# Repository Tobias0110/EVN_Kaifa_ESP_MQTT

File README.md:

# EVN Kaifa to MQTT
Allows you to read data from different kinds of smart power meters used by the
EVN power company in Austria. Data is read from the MBus interface (called Kundenschnittstelle P1),
packages are decrypted and then the values are sent to an MQTT endpoint. The
device hosts a webpage, where you can change your settings.

## 🤔 How does it work?
The ESP8266 receives the MBus data from the smart meter via a UART interface on the
front facing side of the device. A specially developed interface PCB powers the
micro-controller board from the MBus idle voltage (no extra power supply needed).
In addition, it contains a level shifter to convert from MBus voltage levels to
3V3 UART compatible with the ESP8266. This is useful because many people don't
have a power socket near their power meter.

The ESP8266 micro-controller syncs to the smartmeter's bursts of data so no packets
are lost. After receiving a package it is decrypted and the DSLM/COSEM data structure
is parsed to extract the measurement fields. These fields are then sent to an MQTT
broker in a preselected format. All relevant parameters can be configured via the
serial console at startup and are saved to the EEPROM.

Alternatively, you can update your configuration on the webpage that the ESP hosts
on the wifi network. The page is only accessible with a passcode that is set during
first setup. For more details on the webpage see below.

## 🔧 Installation
> **Note**
> Make sure the ESP is not connected to the interface board during programming or
> configuration.

The following steps are applicable if you are using the Arduino IDE to build the
project yourself.

1. Install [NodeJS](https://nodejs.org) on your machine, and navigate to the `www` directory.
   There, install the required npm packages by running `npm i` in your console.
2. Run the webpage build script. This should create a file named `settings-page.html.inl.h`
   next to the Arduino sketch file.
3. Install the ESP-Module as a compilation target.
    1. Add board config repository: File → Preferences →
       Paste URL into "Additional boards manager URLs": [http://arduino.esp8266.com/stable/package_esp8266com_index.json](http://arduino.esp8266.com/stable/package_esp8266com_index.json)
    2. Install the toolchain: Tools → Boards Manager → Install: esp8266
    3. Select the specific ESP module: Tools → Board → ESP2866 Boards → NodeMCU 1.0 (ESP-12E Modul)
4. Open the Library Manager pane and install the following dependecies.
    * [Crypto](https://github.com/rweather/arduino-projects) by Rhys Weatherley
    * [PubSubClient](https://github.com/knolleary/pubsubclient) by Nicholas O'Leary
    * [CRC](https://github.com/RobTillaart/CRC) by Rob Tillaart
5. Manully install the following dependencies by downloading their source code and
   dropping it into your `Arduino/Libraries` directory.
    * [ESPTrueRandom8266](https://github.com/marvinroger/ESP8266TrueRandom) by Marvin Roger
6. Click verify to check if the project builds without errors.
7. Connect the ESP module and click upload like for any other Arduino-like micro controller.
8. Connect to the ESP2866 through the serial monitor and start configuration.

## ⚙ Configuration via serial
> **Note**
> Make sure the ESP is not connected to the interface board during programming or
> configuration.

First configuration of the device is done via the serial terminal and is guided
by an interactive setup wizard. On first startup the checksum check will fail and
you will be required to enter settings. Later, you can enter the setup wizard
again during the first 10 seconds after starting by pressing 's'. You can also
clear your configuration by pressing 'c'.

1. Connect the ESP board via USB to your computer and open a serial terminal.
   Serial settings: 115200 Baud, NO Parity
2. Press reset on the ESP board.
3. On first startup the setup wizard starts immediately. Else press 's' on your
   keyboard when you are prompted to do so to edit the current settings.
4. The configuration wizard shows each settings field. Enter the data for each field
   and press return. Some fields come with default values, which are accepted by
   pressing return without any other input.
5. After start up the system switches the serial interface to MBus mode (2400 baud,
  even parity) and waits for data packets.

To boot the ESP with your settings, reset the micro-controller. All the settings fields that
can be configured are listed in the table below.

| Field name | Default value | Description |
| :--- | :--- | :--- |
WiFi SSID || SSID of the WiFi station to connect to |
WiFI password || Password of the WiFi station to connect to |
MQTT broker network address || Domain/IP of the MQTT broker server |
MQTT broker network port | 1883 | Network port of the MQTT broker server |
MQTT broker certificate fingerprint | [insecure] | SHA1 fingerprint of the SSL certificate of the MQTT broker server as hex string. If set to `[insecure]` TLS is disabled and all data is sent as plaint text |
MQTT broker user name | power-meter | User name to authenticate at the MQTT broker server |
MQTT broker password || Password to authenticate at the MQTT broker server |
MQTT broker client id || Client id to register as at the MQTT broker server |
MQTT broker path || Base path prepended to MQTT topics |
MQTT message mode | 2 | Selects the format for sending the data fields to the MQTT broker server (0 - raw, 1 - topics, 2 - json) |
Webpage key | _automatically generated random value_ | Passkey to access the webpage |
DSLM/COSEM decryption key (meter key) || Decryption key to decipher the MBus data packets provided by the power company |

> **Note**
> When reconnecting the micro-controller PCB to the interface PCB make sure that the pins align correctly.
> Also check that the USB connector points in the direction of the M-Bus connector. Wrong positioning can result in a short and damage the microcontroler.

## 🌍 Configuration via webpage
After initial setup with the serial interface and having the ESP connected to
the wifi, you can connect to the configuration webpage. To access it you need
the passkey you set before.

Due to memory limitation of the ESP8266 only a single TLS tunnel can be used at
once. As one is needed for the secure mqtt connection, there are no resources left
for the webserver. Therefore an alternative security scheme is used and the
page is hosted as plain HTTP. This means, that all your settings are always
transmitted encrypted and unreadable to others.

For security reasons, especially sensitive fields are not automatically populated
in their respective form fields. When you edited any settings and saved your changes
they will only take effect after restarting the device.

## 📬 MQTT output formats
> **Note**
> 🔐 When using secure MQTT, make sure to put `tls_version tlsv1.2` in your MQTT
> servers config file, so it only accepts encrypted connections!

The system can be configured to output the data received from the smartmeter in one
of the following formats.

### 🥩 Raw
The decryptd raw data without DSLM/COSEM parsing is sent to the broker at
`<basepath/raw>`. The data is sent as binary.

### 🐧 JSON
If the data is serialized as JSON, it is sent to the broker at `<basepath>/json`.
The json object has the following format.

| Field name  | Type          | Full name  | Description |
| :---------- | :------------ | :--------- | :--- |
| meternumber | string[12]    || The unique identification number of the smartmeter |
| timestamp   | ISO timestamp || Time when the measurement was taken |
| w_p         | number        | positive total energy | Total energy consumed |
| w_n         | number        | negative total energy | Total energy sent back to the grid |
| p_p         | number        | positive momentary power | Power currently consumed |
| p_n         | number        | negative momentary power | Power currently sent back to the grid |
| u1          | number        | voltage on phase 1 | Momentary voltage measured on phase 1 |
| u2          | number        | voltage on phase 2 | Momentary voltage measured on phase 2 |
| u3          | number        | voltage on phase 3 | Momentary voltage measured on phase 3 |
| i1          | number        | current on phase 1 | Momentary current measured on phase 1 |
| i2          | number        | current on phase 2 | Momentary current measured on phase 2 |
| i3          | number        | current on phase 3 | Momentary current measured on phase 3 |
| phi         | number        | power factor | Momentary power factor |
| ip          | string        || IP address received via DHCP |
| rssi        | string        | Received Signal Strength Indicator | Strength of the wifi signal in `dBm` |

The following JSON is an example package sent by the micro-controller.
```json
{
  "meternumber": "181220000009",
  "timestamp": "2021-09-27T09:47:15+02:00",
  "w_p": 12937,
  "w_n": 0,
  "p_p": 0,
  "p_n": 0,
  "u1": 233.7,
  "u2": 0,
  "u3": 0,
  "i1": 0,
  "i2": 0,
  "i3":0 ,
  "phi":1.000,
  "ip": "192.168.143.51",
  "rssi": "-52dBm"
}
```

### 🔬 Individual topics
If the data fields are sent to individual mqtt topics the following paths are used.
For a description of the fields checkout the section above.

| Field name               | Full name  |
| :----------------------- | :--------- |
| `<basepath>/meternumber` ||
| `<basepath>/timestamp`   ||
| `<basepath>/w_p`         | positive total energy |
| `<basepath>/w_n`         | negative total energy |
| `<basepath>/p_p`         | positive momentary power |
| `<basepath>/p_n`         | negative momentary power |
| `<basepath>/u1`          | voltage on phase 1 |
| `<basepath>/u2`          | voltage on phase 2 |
| `<basepath>/u3`          | voltage on phase 3 |
| `<basepath>/i1`          | current on phase 1 |
| `<basepath>/i2`          | current on phase 2 |
| `<basepath>/i3`          | current on phase 3 |
| `<basepath>/phi`         | power factor |

## ☔ Standard compliance
The parsing of MBus packets, and the deserialization of the DSLM/COSEM data is
based on reverse engineering work done by [@Tobias0110](https://www.github.com/Tobias0110)
and [@PreyMa](https://www.github.com/PreyMa) as the documents defining the standard are not
publicly accessible. So there is no guarantee that anything behaves as expected,
but we try to thoroughly test the software on real hardware.

Thanks to Austrian laws power companies are required to describe how the P1 interface
on their smartmeters works at least to some degree. The following resources were
useful to understand how the communication should be implemented:

* [M-Bus Specification](https://m-bus.com/assets/downloads/MBDOC48.PDF) (version "late 90s"):
* Smart meter customer data port description (Multiple Austrian energy companies):
  * [EVN](https://www.netz-noe.at/Download-(1)/Smart-Meter/218_9_SmartMeter_Kundenschnittstelle_lektoriert_14.aspx)
  * [Stadtwerke Schwaz](https://stadtwerkeschwaz.at/pdfs/Technische%20Beschreibung%20Kundenschnittstelle%20SWS%20Smart%20Meter.pdf)
  * [Salzburg Netz](https://www.salzburgnetz.at/content/dam/salzburgnetz/dokumente/stromnetz/Technische-Beschreibung-Kundenschnittstelle.pdf)
  * [Tinetz](https://www.tinetz.at/infobereich/smart-meter/anleitungen-fragen-antworten/?no_cache=1&tx_bh_page%5Baction%5D=download&tx_bh_page%5Bcontroller%5D=File&tx_bh_page%5Bfile%5D=101&cHash=7b38017b8f4066394c0f5119ee1ae342)
* Python implementation of a [DLMS to XML converter](https://github.com/Gurux/Gurux.DLMS.Python/)

## ⚒ Hardware

New in Version 2:
* M-Bus over voltage protection: Protects the DC/DC converter from voltages outside its specs.
* EMC improvements of the DC/DC converter.
* Space for alternative Zener diodes to allow diffrent logic levels on the M-Bus.
* Big capacitor can be alternatively placed on the bottom side of the PCB.
* Markings for how to connect the microcontroller correctly.
* Warning to disconnect the microcontroller for programming is now on the bottom side.

## 📋 Feature roadmap
* [X] Output the clock of the smart meter in UTC
* [X] Output the smartmeter's unique id (Zählernummer)
* [X] Implement the M-Bus library and parse DSLM/COSEM data
* [X] MQTT SSL
* [X] Web server for configuration
* [ ] Expand the software to support all M-Bus smart meters in Austria
* [ ] Support for the Improv Serial standard for WiFi configuration

## 🤝 Support the project
You can support the project by purchasing the custom hardware designed by @Tobias0110.
Contact Tobias via oe3tec(at)egimoto.com

If you want to contribute to the project feel free to hack on the code and open a
pull-request. Let us know if you find any bugs or issues.

## 📜 License
This project is licensed under the GPL v2.0.

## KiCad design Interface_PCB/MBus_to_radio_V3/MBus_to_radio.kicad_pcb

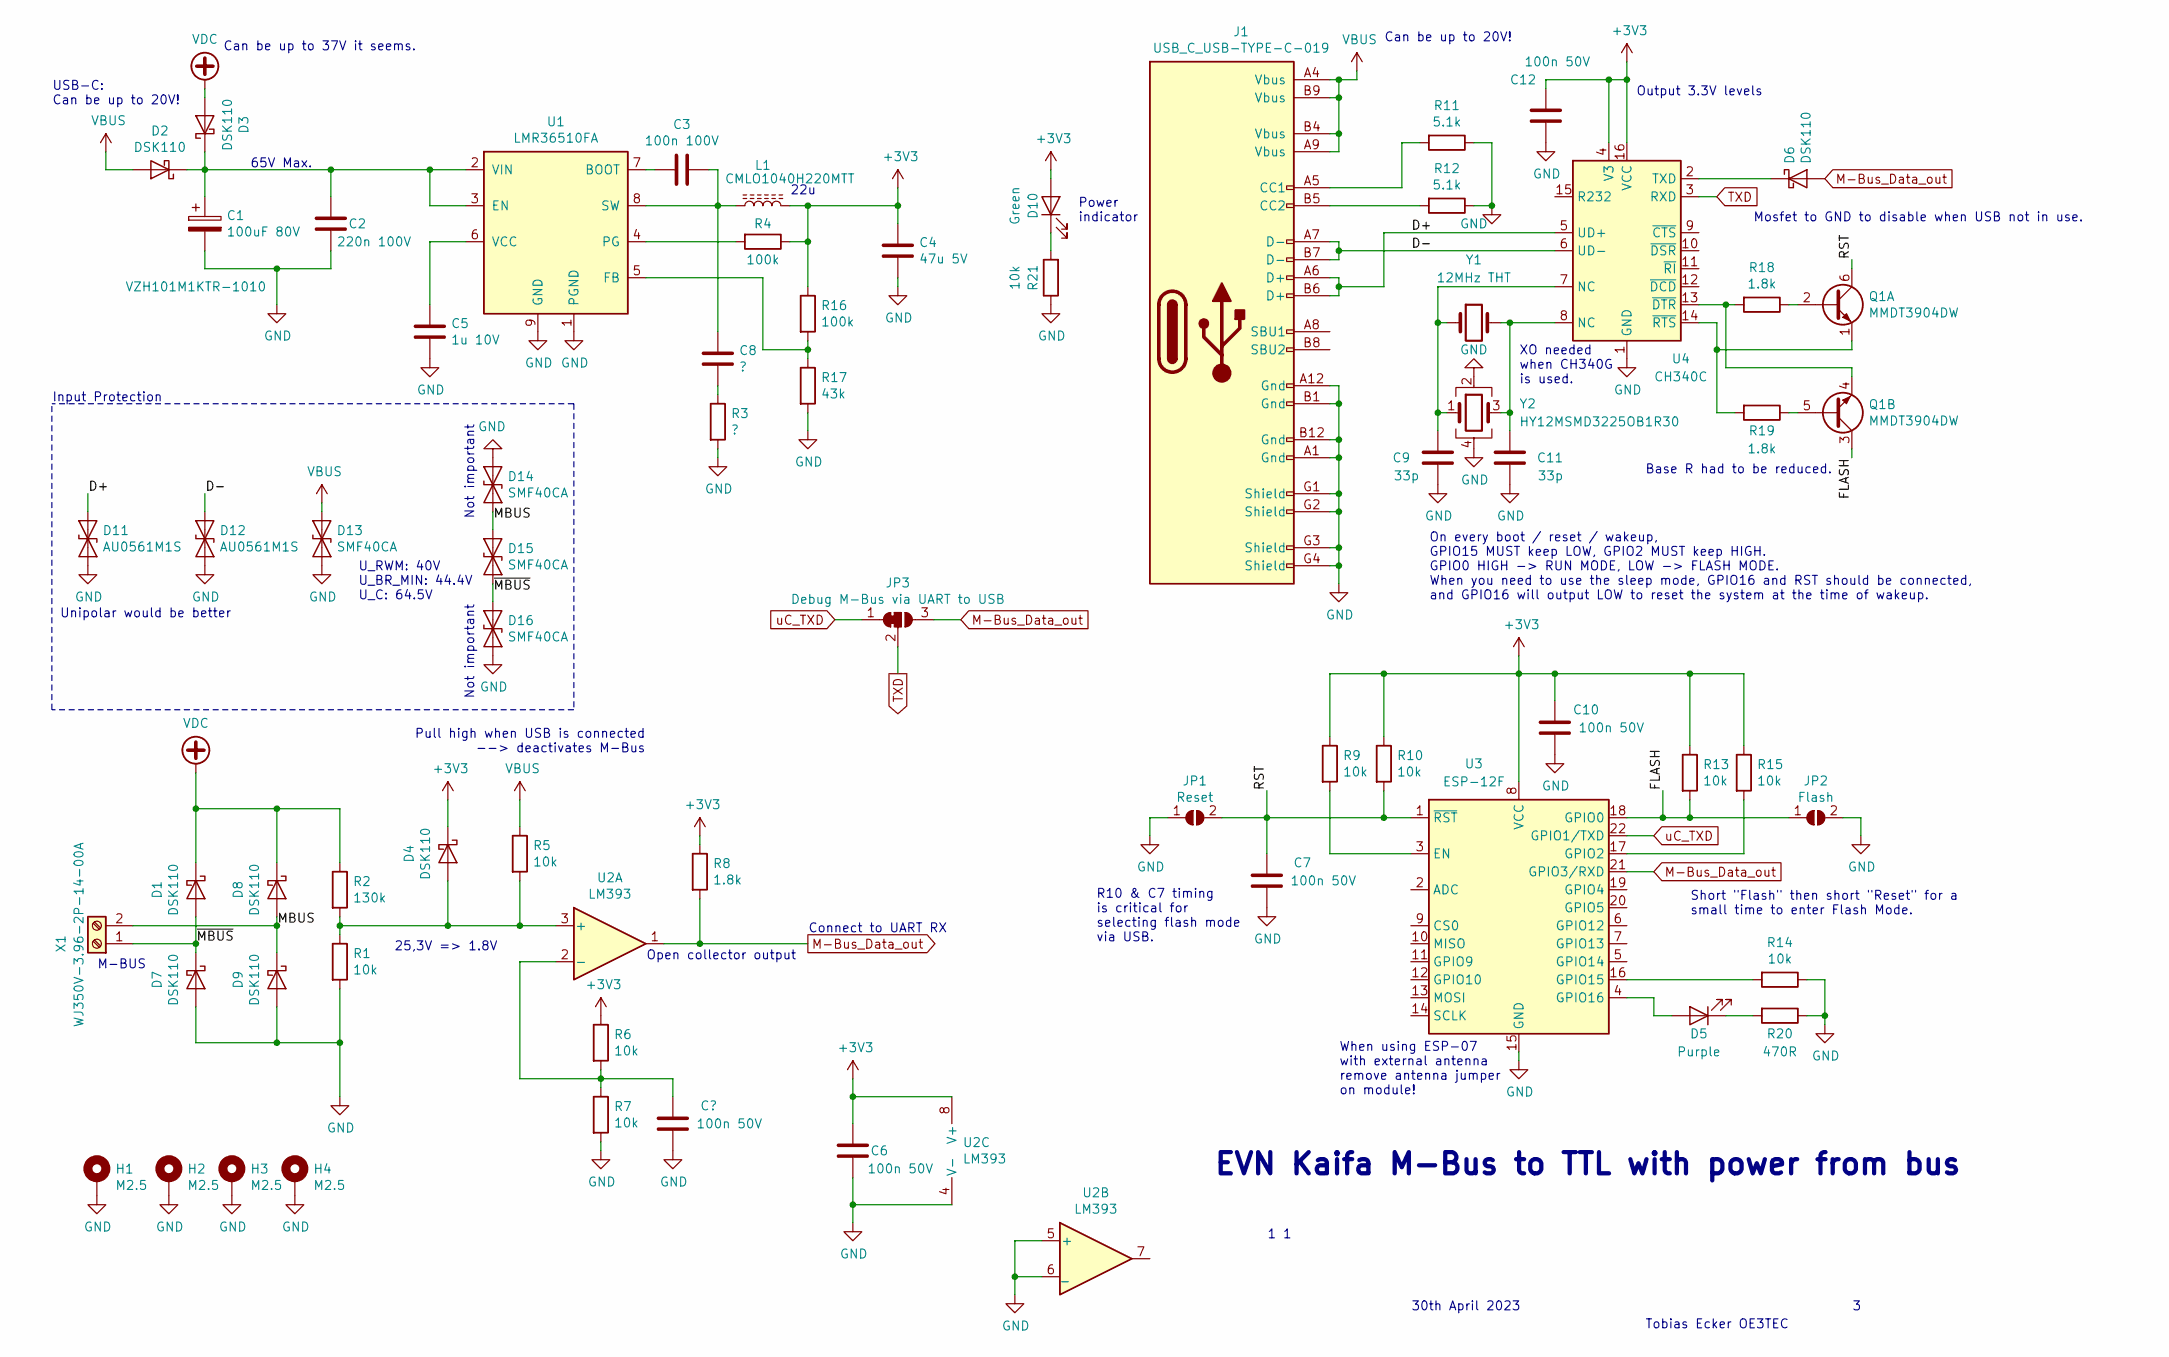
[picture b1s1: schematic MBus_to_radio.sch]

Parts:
C1: 100uF 80V; CP_Elec_10x10
C2: 220n 100V; C_1206_3216Metric
C3: 100n 100V; C_0603_1608Metric
C4: 47u 5V; C_1206_3216Metric
C5: 1u 10V; C_0603_1608Metric
C6, C7, C10, C12: 100n 50V; C_0603_1608Metric
C8: ?; C_0603_1608Metric
C9, C11: 33p; C_0402_1005Metric
D1, D2, D3, D4, D6, D7, D8, D9: DSK110; D_SOD-123
D5: Purple; LED_0402_1005Metric
D10: Green; LED_0402_1005Metric
D11, D12: AU0561M1S; D_0402_1005Metric
D13, D14, D15, D16: SMF40CA; D_SOD-123F
H1, H2, H3, H4: M2.5; MountingHole_2.5mm_Pad_Via
J1: USB_C_USB-TYPE-C-019; USB-TYPE-C-019
JP1: Reset; SolderJumper-2_P1.3mm_Open_RoundedPad1.0x1.5mm
JP2: Flash; SolderJumper-2_P1.3mm_Open_RoundedPad1.0x1.5mm
JP3: Debug M-Bus via UART to USB; SolderJumper-3_P1.3mm_Bridged12_RoundedPad1.0x1.5mm_NumberL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
L1: CMLO1040H220MTT; L_10.4x10.4_H4.8
Q1: MMDT3904DW; SOT-363_SC-70-6
R1: 10k; R_0603_1608Metric
R2: 130k; R_0603_1608Metric
R3: ?; R_0603_1608Metric
R4: 100k; R_0603_1608Metric
R5, R6, R7, R9, R10, R13, R14, R15, R21: 10k; R_0402_1005Metric
R8, R18, R19: 1.8k; R_0402_1005Metric
R11, R12: 5.1k; R_0402_1005Metric
R16: 100k; R_0402_1005Metric
R17: 43k; R_0402_1005Metric
R20: 470R; R_0402_1005Metric
U1: LMR36510FA; SOIC-8-1EP_3.9x4.9mm_P1.27mm_EP2.29x3mm_ThermalVias
U2: LM393; SOIC-8_3.9x4.9mm_P1.27mm
U3: ESP-12F; ESP-12E
U4: CH340C; SOIC-16_3.9x9.9mm_P1.27mm
X1: WJ350V-3.96-2P-14-00A
Y1: 12MHz THT; Crystal_HC49-U_Vertical
Y2: HY12MSMD3225OB1R30; Crystal_SMD_EuroQuartz_MT-4Pin_3.2x2.5mm

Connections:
+3V3: C4.2, C6.2, C10.2, C12.2, D4.1 (K), D10.2 (A), L1.2, R4.1, R6.1, R8.1, R9.1, R10.1, R13.1, R15.1, R16.1, U2.8 (V+), U3.8 (VCC), U4.4 (V3), U4.16 (VCC)
/D+: D11.1 (A1), J1.A6 (D+), J1.B6 (D+), U4.5 (UD+)
/D-: D12.1 (A1), J1.A7 (D-), J1.B7 (D-), U4.6 (UD-)
/FLASH: JP2.1 (A), Q1.3 (C2), R13.2, U3.18 (GPIO0)
/MBUS: D8.2 (A), D9.1 (K), D14.2 (A2), D15.1 (A1), X1.2
/RST: C7.2, JP1.2 (B), Q1.6 (C1), R10.2, U3.1 (~RST)
/~MBUS: D1.2 (A), D7.1 (K), D15.2 (A2), D16.1 (A1), X1.1
GND: C1.2, C2.1, C4.1, C5.1, C6.1, C7.1, C9.1, C10.1, C11.1, C12.1, D7.2 (A), D9.2 (A), D11.2 (A2), D12.2 (A2), D13.2 (A2), D14.1 (A1), D16.2 (A2), H1.1, H2.1, H3.1, H4.1, J1.A1 (Gnd), J1.A12 (Gnd), J1.B1 (Gnd), J1.B12 (Gnd), J1.G1 (Shield), J1.G2 (Shield), J1.G3 (Shield), J1.G4 (Shield), JP1.1 (A), JP2.2 (B), R1.2, R3.2, R7.2, R11.1, R12.1, R14.1, R17.2, R20.1, R21.1, U1.1 (PGND), U1.9 (GND), U2.4 (V-), U2.5 (+), U2.6 (_), U3.15 (GND), U4.1 (GND), Y2.2, Y2.4
M-Bus_Data_out: D6.2 (A), JP3.3 (B), R8.2, U2.1, U3.21 (GPIO3/RXD)
unnamed: C1.1, C2.2, D2.1 (K), D3.1 (K), U1.2 (VIN), U1.3 (EN)
unnamed: C3.1, U1.7 (BOOT)
unnamed: C3.2, C8.2, L1.1, U1.8 (SW)
unnamed: C5.2, U1.6 (VCC)
unnamed: C8.1, R3.1
unnamed: C9.2, U4.7 (NC), Y1.1, Y2.1
unnamed: C11.2, U4.8 (NC), Y1.2, Y2.3
unnamed: D4.2 (A), R1.1, R2.2, R5.2, U2.3 (+)
unnamed: D5.1 (K), R20.2
unnamed: D5.2 (A), U3.4 (GPIO16)
unnamed: D6.1 (K), U4.2 (TXD)
unnamed: D10.1 (K), R21.2
unnamed: J1.A5 (CC1), R11.2
unnamed: J1.B5 (CC2), R12.2
unnamed: Q1.1 (E1), R19.2, U4.14 (~RTS)
unnamed: Q1.2 (B1), R18.1
unnamed: Q1.4 (E2), R18.2, U4.13 (~DTR)
unnamed: Q1.5 (B2), R19.1
unnamed: R4.2, U1.4 (PG)
unnamed: R6.2, R7.1, U2.2 (-)
unnamed: R9.2, U3.3 (EN)
unnamed: R14.2, U3.16 (GPIO15)
unnamed: R15.2, U3.17 (GPIO2)
unnamed: R16.2, R17.1, U1.5 (FB)
TXD: JP3.2 (C), U4.3 (RXD)
VBUS: D2.2 (A), D13.1 (A1), J1.A4 (Vbus), J1.A9 (Vbus), J1.B4 (Vbus), J1.B9 (Vbus), R5.1
VDC: D1.1 (K), D3.2 (A), D8.1 (K), R2.1
uC_TXD: JP3.1 (A), U3.22 (GPIO1/TXD)

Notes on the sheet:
EVN Kaifa M-Bus to TTL with power from bus
1 1
30th April 2023
Tobias Ecker OE3TEC
Connect to UART RX
Pull high when USB is connected --> deactivates M-Bus
Open collector output
Short "Flash" then short "Reset" for a small time to enter Flash Mode.
25,3V => 1.8V
On every boot / reset / wakeup, GPIO15 MUST keep LOW, GPIO2 MUST keep HIGH. GPIO0 HIGH -> RUN MODE, LOW -> FLASH MODE. When you need to use the sleep mode, GPIO16 and RST should be connected, and GPIO16 will output LOW to reset the system at the time of wakeup.
65V Max.
XO needed when CH340G is used.
Output 3.3V levels
R10 & C7 timing is critical for selecting flash mode via USB.
When using ESP-07 with external antenna remove antenna jumper on module!
M-BUS
Power indicator
22u
Can be up to 20V!
USB-C: Can be up to 20V!
Can be up to 37V it seems.
Input Protection
U_RWM: 40V U_BR_MIN: 44.4V U_C: 64.5V
Not important
Unipolar would be better
Base R had to be reduced.
Mosfet to GND to disable when USB not in use.

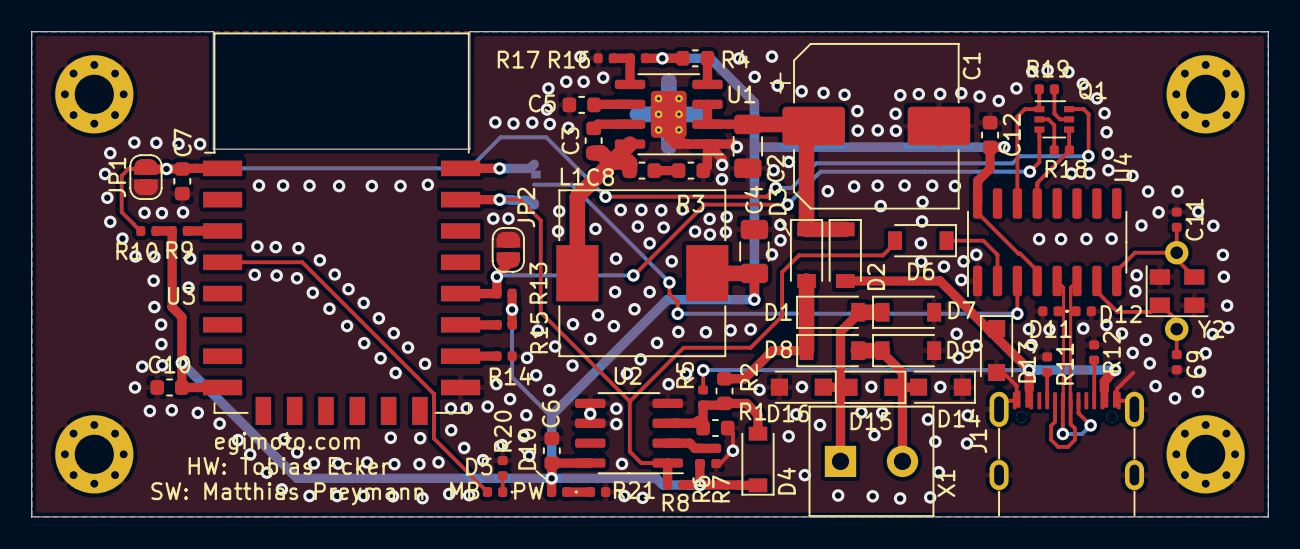
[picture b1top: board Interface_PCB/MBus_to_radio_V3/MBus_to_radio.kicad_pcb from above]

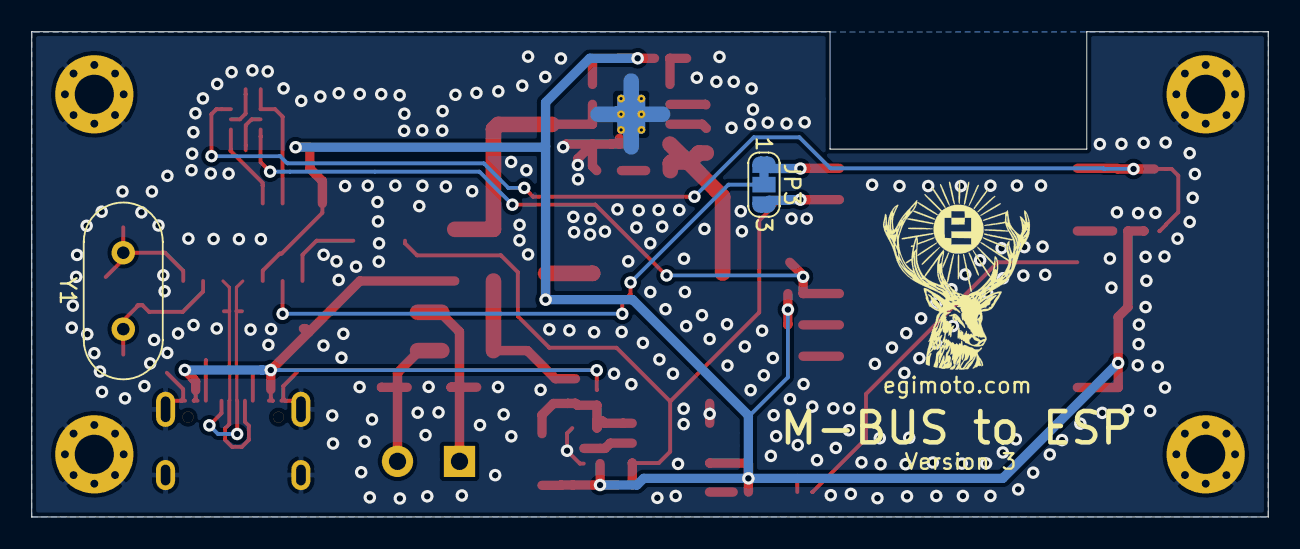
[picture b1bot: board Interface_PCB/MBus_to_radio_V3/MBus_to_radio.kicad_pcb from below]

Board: 2 copper layers, 79.0 x 31.0 mm, 66 parts (2 on the bottom side), 37 nets.

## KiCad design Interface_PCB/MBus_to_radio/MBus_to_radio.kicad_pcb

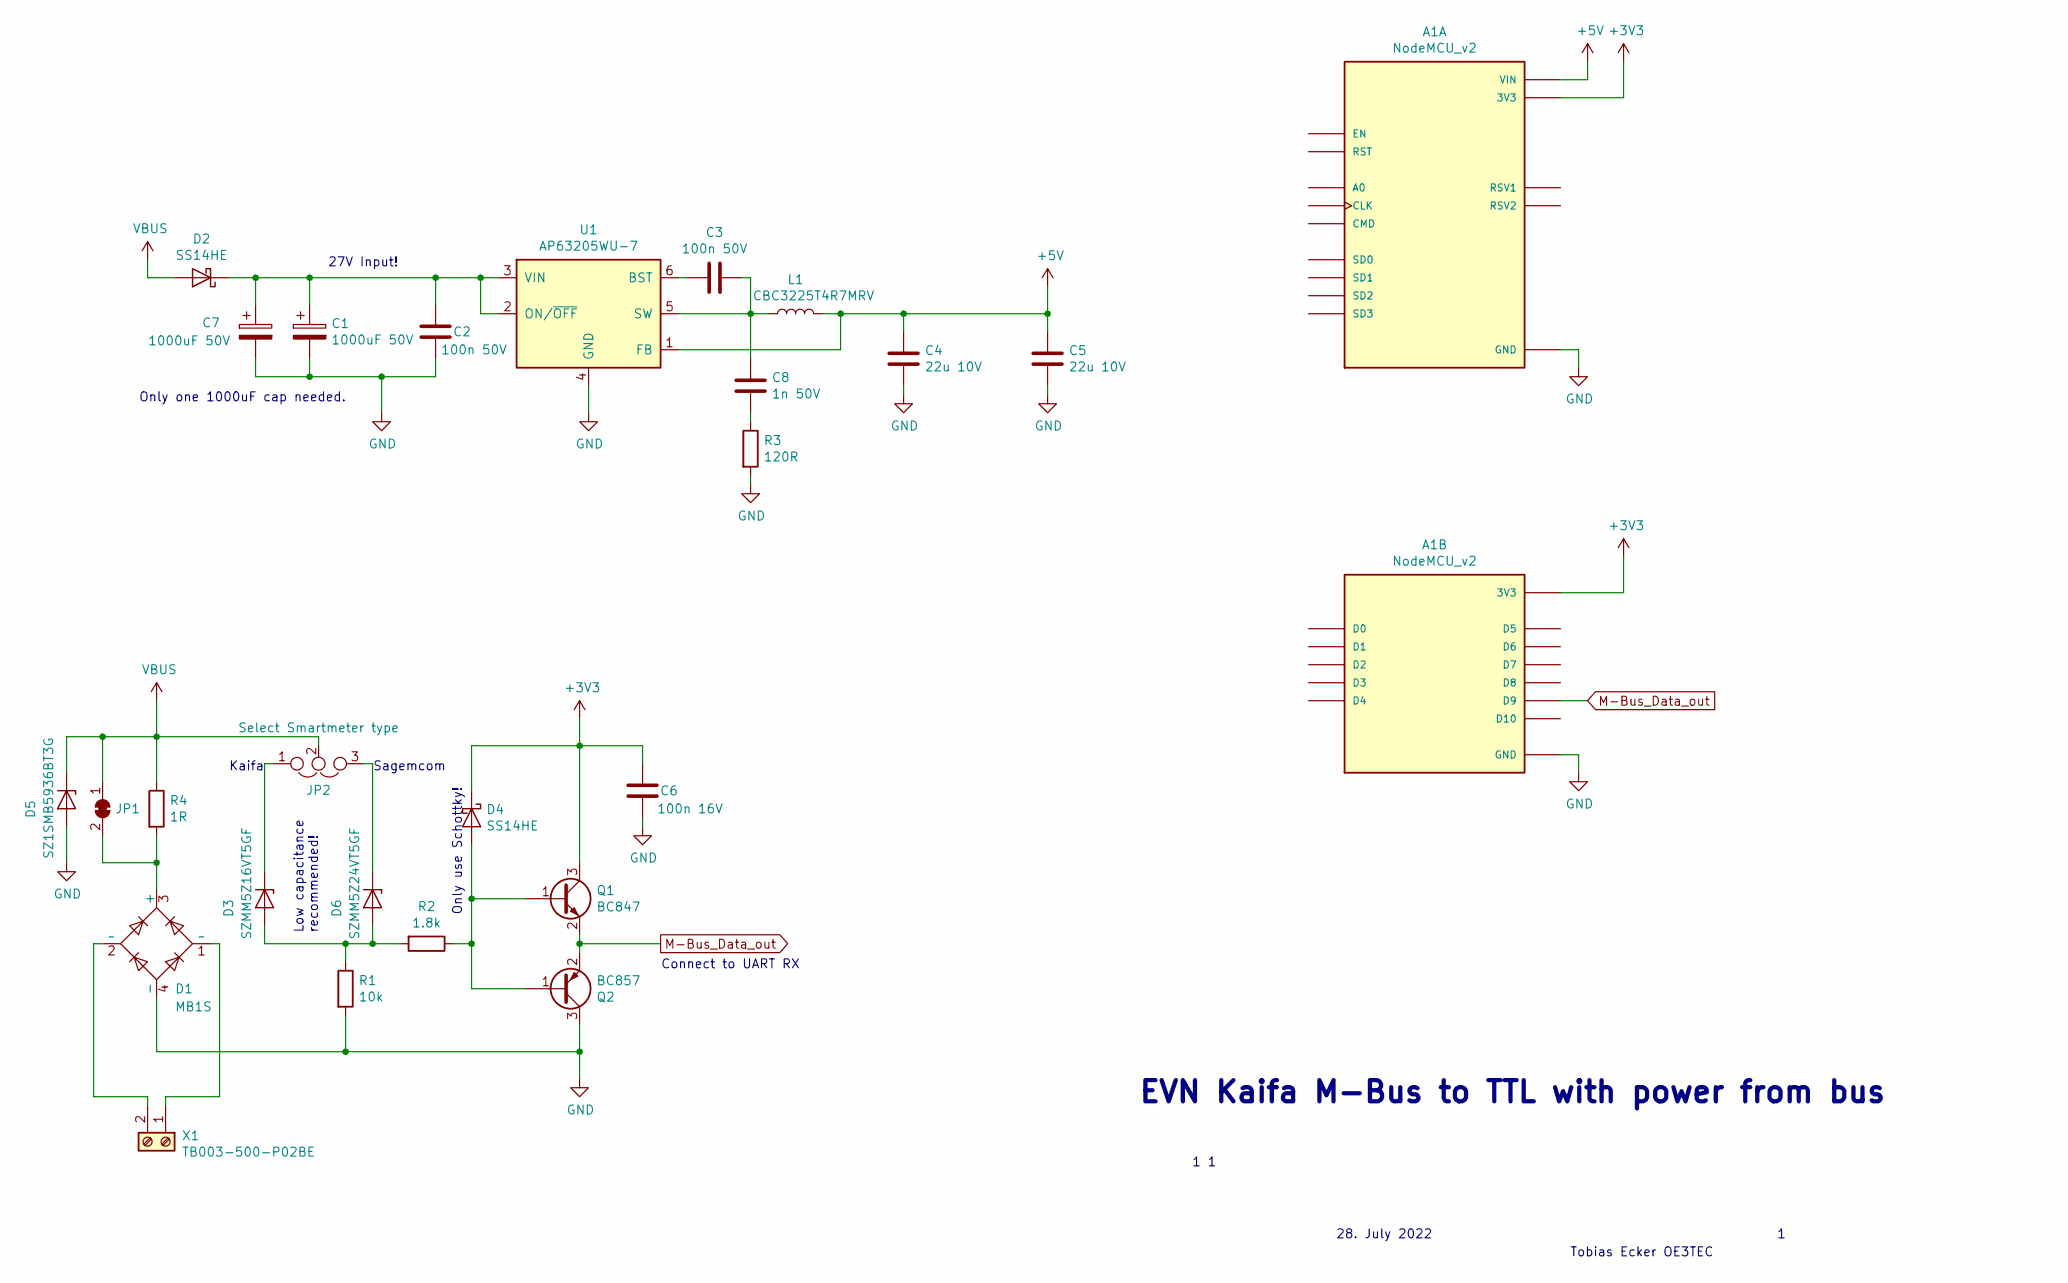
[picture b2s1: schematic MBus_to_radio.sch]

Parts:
A1: NodeMCU_v2; SEEED_113990105; PARTREV N/A
C1, C7: 1000uF 50V; CP_Radial_D10.0mm_P5.00mm
C2, C3: 100n 50V; C_0603_1608Metric
C4, C5: 22u 10V; C_1206_3216Metric
C6: 100n 16V; C_0603_1608Metric
C8: 1n 50V; C_0603_1608Metric
D1: MB1S; TO-269AA
D2, D4: SS14HE; D_SOD-323
D3: SZMM5Z16VT5GF; D_SOD-523
D5: SZ1SMB5936BT3G; D_SMB-SMC_Universal_Handsoldering
D6: SZMM5Z24VT5GF; D_SOD-523
JP1: SolderJumper_2_Bridged; SolderJumper-2_P1.3mm_Bridged_RoundedPad1.0x1.5mm
JP2: Select Smartmeter type; PinHeader_1x03_P2.54mm_Vertical
L1: CBC3225T4R7MRV; L_1210_3225Metric
Q1: BC847; SOT-23
Q2: BC857; SOT-23
R1: 10k; R_0603_1608Metric
R2: 1.8k; R_0603_1608Metric
R3: 120R; R_0603_1608Metric
R4: 1R; R_1812_4532Metric
U1: AP63205WU-7; TSOT-23-6
X1: TB003-500-P02BE; CUI_TB003-500-P02BE

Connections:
+3V3: A1.J1_11 (3V3), A1.J2_6 (3V3), A1.J2_15 (3V3), C6.2, D4.1 (K), Q1.3 (C)
+5V: A1.J1_15 (VIN), C4.2, C5.2, L1.2, U1.1 (FB)
GND: A1.J1_10 (GND), A1.J1_14 (GND), A1.J2_7 (GND), A1.J2_14 (GND), C1.2, C2.1, C4.1, C5.1, C6.1, C7.2, D1.4 (-), D5.2 (A), Q2.3 (C), R1.2, R3.2, U1.4 (GND)
M-Bus_Data_out: A1.J2_12 (D9), Q1.2 (E), Q2.2 (E)
unnamed: C1.1, C2.2, C7.1, D2.1 (K), U1.2 (ON/~OFF), U1.3 (VIN)
unnamed: C3.1, U1.6 (BST)
unnamed: C3.2, C8.2, L1.1, U1.5 (SW)
unnamed: C8.1, R3.1
unnamed: D1.1 (~~), X1.1
unnamed: D1.2 (~~), X1.2
unnamed: D1.3 (+), JP1.2 (B), R4.2
unnamed: D3.1 (K), JP2.1
unnamed: D3.2 (A), D6.2 (A), R1.1, R2.2
unnamed: D4.2 (A), Q1.1 (B), Q2.1 (B), R2.1
unnamed: D6.1 (K), JP2.3
VBUS: D2.2 (A), D5.1 (K), JP1.1 (A), JP2.2, R4.1

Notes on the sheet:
EVN Kaifa M-Bus to TTL with power from bus
1 1
28. July 2022
Tobias Ecker OE3TEC
Only use Schottky!
Low capacitance recommended!
Connect to UART RX
27V Input!
Only one 1000uF cap needed.
Kaifa
Sagemcom

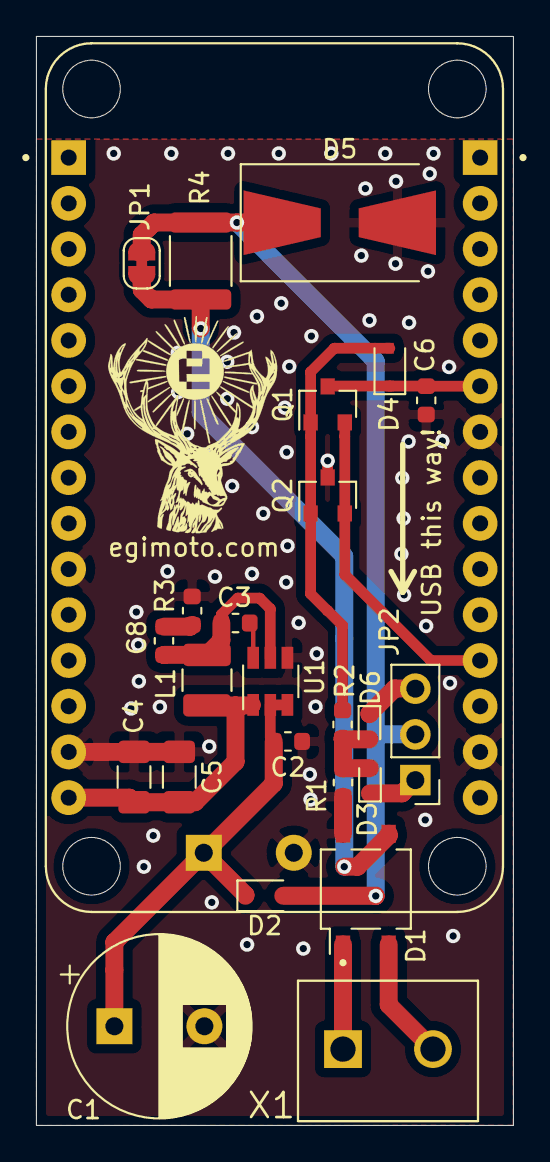
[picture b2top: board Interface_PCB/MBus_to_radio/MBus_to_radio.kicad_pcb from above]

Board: 2 copper layers, 26.5 x 60.5 mm, 26 parts (1 on the bottom side), 16 nets.

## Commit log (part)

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2022-11-07 starting to combine code of test projects
2022-11-07 Update PCB infos
2022-11-07 added PCB data
2022-11-08 added pictures
2022-11-29 Add links to resources as comment block
2022-11-29 Include different stuff when building in mock-mode
2022-11-29 Add integer type aliases
2022-11-29 Add NoStl::Optional<T>
2022-11-29 Add NoStl::UniquePtr<T>
2022-11-29 Add SerenityOS style error handling
    SerenityOS uses an ErrorOr<T> return value in fallible functions instead of exceptions. We don't have exceptions either so let's do the same (without manually turning them on and unnecessary increasi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
2022-11-29 Add Buffer base class
2022-11-29 Add LocalBuffer<int> and OwnedBuffer
2022-11-29 Add BufferReader
2022-11-29 Add SerialBufferReader<T>
2022-11-29 Add dummy setup() and loop() functions
2022-11-29 Add m-bus frame parsing
    Each m-bus link frame contains a m-bus transport frame.
2022-11-29 Add dlms frame decryption
    Parsing this frame makes a few assumptions, like the type of link frame and the decryption mode
2022-11-29 Add abstract MqttSender base class
2022-11-29 Implement cosem data parsing
    Extract cosem data like line voltage, current and phase shift from the dlms structure.
2022-11-29 Add MqttJsonSender
2022-11-30 Add EEPROM storage slots to store settings
2022-11-30 Remove template parameter name in forward declaration
2022-11-30 Remove some whitespace
2022-11-30 Implement the setup and loop functions
2022-11-30 Use the key stored in the settings to decrypt
2022-12-02 Add isEmpty() getter to BufferPrinter
2022-12-02 Implement serial setup wizard
    This allows to configure the gateway on setup via a serial terminal and store the settings in its eeprom.
2022-12-02 Large scale code formatting
    Visual studio suddenly thought it wants to reformat everything.
2022-12-11 Implement optional debug printing for esp builds
2022-12-11 Debug print the wifi IP
2022-12-11 Debug print during mqtt setup
2022-12-11 Fix shadowed `showSetup` flag and remove case sensitivity
2022-12-11 Clear out serial input buffer before starting setup wizard
2022-12-11 Rename vars in waitForAndProcessPacket to be confided
    After `TRYGET` the variables are guaranteed to contain values instead of errors.
2022-12-11 Make connecting to the mqtt broker fallible
2022-12-22 Fix use after free of the mqtt server address
    The PubSubClient library allows to set the domain of the mqtt server to connect to as a string. However, it only stores a pointer and does not copy the contents into an owned buffer. Therefore, the s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
2022-12-22 Use a lower serial timeout that might actually fire
    The implementation of the Serial lib for ESP8266 has a silent limit for timeouts. If a timeout larger than 26.8s is encountered, the internally polled timer will never expire.
2022-12-22 Give a better assertion error message
2022-12-22 Add debug printing to MqttJsonSender
2022-12-22 Extend DummySerial interface
    Add two missing methods to make the code work on Desktop again.
2022-12-22 DummySerial: Return the number of read bytes
    The old loop decremented the `bytesToRead` resulting in a return value of 0 all the time.
2022-12-22 Implement simple validation for settings fields
2022-12-26 Allow uniquePtr conversion of compatible pointer types
    This is useful for pointer conversions of subclasses.
2022-12-26 Add `makeUnique()` function
2022-12-26 Add TLS for mqtt connections
2022-12-26 Terminate serial data with CR and NL
2022-12-26 Remove "ip" from name of `Settings::MqttBrokerAddress`
    The address could also be a domain name.
2022-12-26 Move length validation into reusable lambda
2022-12-26 Update version number
2022-12-26 Update the readme
2022-12-26 Properly format nested ordered lists
2022-12-27 Assert the EEPROM loads enough data into memory
2022-12-27 update PCB V2 to version that was produced
2022-12-27 add warnings to README.md
2022-12-28 Readme: Make images a bit smaller
    It would be nice, if this could be done without inline HTML...
2022-12-28 Add support for backspace in `readSerialLine()`
2022-12-28 Null terminate buffer before validation
2022-12-28 Allow for space characters when reading a line of hex data
2022-12-28 Make clear which kind of ssl certificate fingerprint is required
2022-12-28 Make certificate fingerprint a secure field
2022-12-28 Null terminate buffer after hex string compaction
2022-12-28 Add IndexReader class for buffer parsing
2022-12-29 DummySerial: Return if console bytes are available
    This does not work perfectly, but with this `flushSerial()` can actually clear out the console buffer. However, it sometimes hangs the program as `WaitForSingleObject()` returns true, but `getch_()` 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
2022-12-29 SerialBufferReader: Allow for different packet delimiters
2022-12-29 Buffer: Add base64 decoding
2022-12-29 Settings: Implement eeprom storage helpers for DER files
2022-12-29 Stop `readLine()` also at NL
    This helps when pasting PEM files into the terminal.
2022-12-29 Implement configuration wizard for web server ssl cert & key
2022-12-29 Set serial timeout for setup wizard
2022-12-29 Read complete pem file footer line
2022-12-30 Reset both der buffers after decoding base64
2022-12-30 Assert that der file length is not larger than the settings field
2022-12-30 Add some simple mqtt domain name validation
    This validation is not exhaustive as it does not check each subdomain component. But it at least should help to prevent most typos when entering.
2022-12-30 Send RSSI and IP in JSON mqtt messages
2022-12-30 ReadMe: Explain the additional mqtt JSON fields
2023-01-09 Correctly print DummyIPAddress
2023-01-09 Settings: Allow for pointers into the EEPROM buffer
    Do not copy every string out of the EEPROM object into a separate buffer. Instead just create a buffer object with a pointer into the EEPROM handle buffer, if it is a read-only operation. To prevent 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
    This change will come in handy for reading DER cert and key files stored in the EEPROM, which only need to be read by BearSSL during start up. In the future all of the EEPROM buffer memory should be 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
2023-01-09 End the EEPROM at the end of startup
    This frees the mutable memory buffer held in memory.
2023-01-09 Add simple web server
2023-01-10 Switch on the LED during setup
2023-01-10 Do the wifiClient/Server unblocking during the LED flicker time
    Instead of wasting100ms, do the wifi unblocking during this time, and just wait the remaining time at the end.
2023-01-11 Correctly check der buffer file length after decoding
2023-01-11 Add DerFile class
2023-01-11 Allow switching to custom webserver cert and key
2023-01-16 Let buffer parse methods take a reference instead of copying the reader
2023-01-16 BufferReaders: Differentiate fallible methods by name
    Make it clear in the interface which methods can fail (return ErrorOr<>). This makes reader types interchangeable in templated parser functions, as the basic BufferReader implements both interface ty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
2023-01-16 BufferPrinter: Allow sub classes to handle full state
    By overriding the `onBufferFull()` method, a subclass may handle the full state during printing. The method has to clear the internal buffer and return true on success.
2023-01-16 BufferPrinter: Add barebones stream api
2023-01-16 DummyWebServerSecure: Extend interface a lot
    Add many methods needed to simulate the webserver handling requests.
2023-01-16 Buffer: Add Base64 parsing
2023-01-16 WebAuthCookie: Add webserver authentication cookie handling
2023-01-16 Visual Studio code formatting
    I changed my formatter settings, so the changes are pretty messy.
2023-01-18 WebPage: Add renderer
2023-01-18 SettingsField: Add enum for mqtt message modes
2023-01-18 Settings: Add EEPROMHandle class
    This is a RAII helper to automatically call `EEPROM.end()`.
2023-01-18 DummyEEPROM: Allow for multiple begin/end calls
    Do not free the buffer during calls to `.end()` to allow for later `.begin()` calls to access the buffer data. Also be more strict about whether `.begin()` was even called in the first place.
2023-01-18 Settings: Prevent EEPROM from marking itself dirty during reads
    Use `.getConstDataPtr()` in methods that only do reads, to prevent the EEPROM object from marking itself as dirty and committing to the cells on closing.
2023-01-18 Buffer: Add method for html encoding
2023-01-18 WebPage: Add settings page for viewing only
    Settings cannot be changed yet.
2023-01-20 EEPROMHandle: Allow for moving to transfer handle
    This allows to prevent multiple handles being created, needlessly initializing the eeprom multiple times. Instead a single instance can be passed around and destroyed at the very end.
2023-01-28 NoStl: Add type erasing function reference class
    The `FunctionRef<>` class allows taking lambdas that capture variables without the need to make them templates. The class uses an internal template specialized through the constructor parameter and i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
2023-01-28 WebPage: Add optional message to the settings page
    This will be useful for error and success messages when changing a setting eg. validation errors for bad data in a form field
2023-01-28 WebPage: Add wifi password repeat field and prevent vertical stretching
2023-01-28 Doc: Fix typo in comment
2023-01-28 webRequestIsAuthenticated: Fix typo in function name
2023-01-29 WebPage: Implement changing of wifi settings
    The field validation, loading and storing of eeprom settings, and the rendering of the page could be generalized for the other settings forms.
2023-01-29 WebPage: Link wifi repeated pwd field to correct label
2023-01-30 webRenderSettingsPage: Always have the eeprom handle provided
2023-01-30 WebPageRenderer: Rename specialized type alias
    This matches the `EEPROMHandleType` type alias.
2023-01-30 DummyWebServerSecure: Return const refs to args to closer match real implementation
    The internal data structure needs to store `String` objects instead of `std::string`, as creating them on the fly locally results in returning a stale reference. `String` is currently not compatible 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
2023-01-30 WebPage: Implement changing of mqtt settings
2023-02-01 WebPage: Remove http header logging
2023-02-01 WebPage: Add reset button to each form
2023-02-01 WebPage: Add logout functionality
2023-02-01 WebPage: Fix typo in form submit buttons
2023-02-01 WebPage: Add a confirmation message before restarting
2023-02-01 Mocking: Move dummy defines to the top
2023-02-01 Doc: Reorganize comments describing the mocking code
2023-02-01 Move the binary file to a release tag
2023-07-09 FuncRef: Make MSVC compile the storage buffer
    Is this a compiler bug? Writing everything inline does not compile, with the compiler complaining the "As" parameter pack was not expanded, which it very much is. GCC does not trip over this.
2023-07-09 WebPage: Rip out HTTPS
    As it turns out the ESP8266 does not have enough RAM to handle TLS for both the mqtt connection and a fully fledged HTTPS webserver. This means a different more lightweight solution is needed, as the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
2023-08-07 WebPage: Add browser cache control headers
2023-08-07 Doc: Bump copyright year
2023-08-07 Settings: Update CRC32 library
    The methods `enableYield` and `getCRC` are deprecated.
2023-08-07 Settings: Fix insecure mqtt mode
2023-08-11 Update the readme
    Add some infos about the webpage
2023-08-11 Readme: Fix typos and spelling
2023-08-11 Readme: Add build instructions for the static webpage
2023-08-11 Doc: Finally bump the version number
